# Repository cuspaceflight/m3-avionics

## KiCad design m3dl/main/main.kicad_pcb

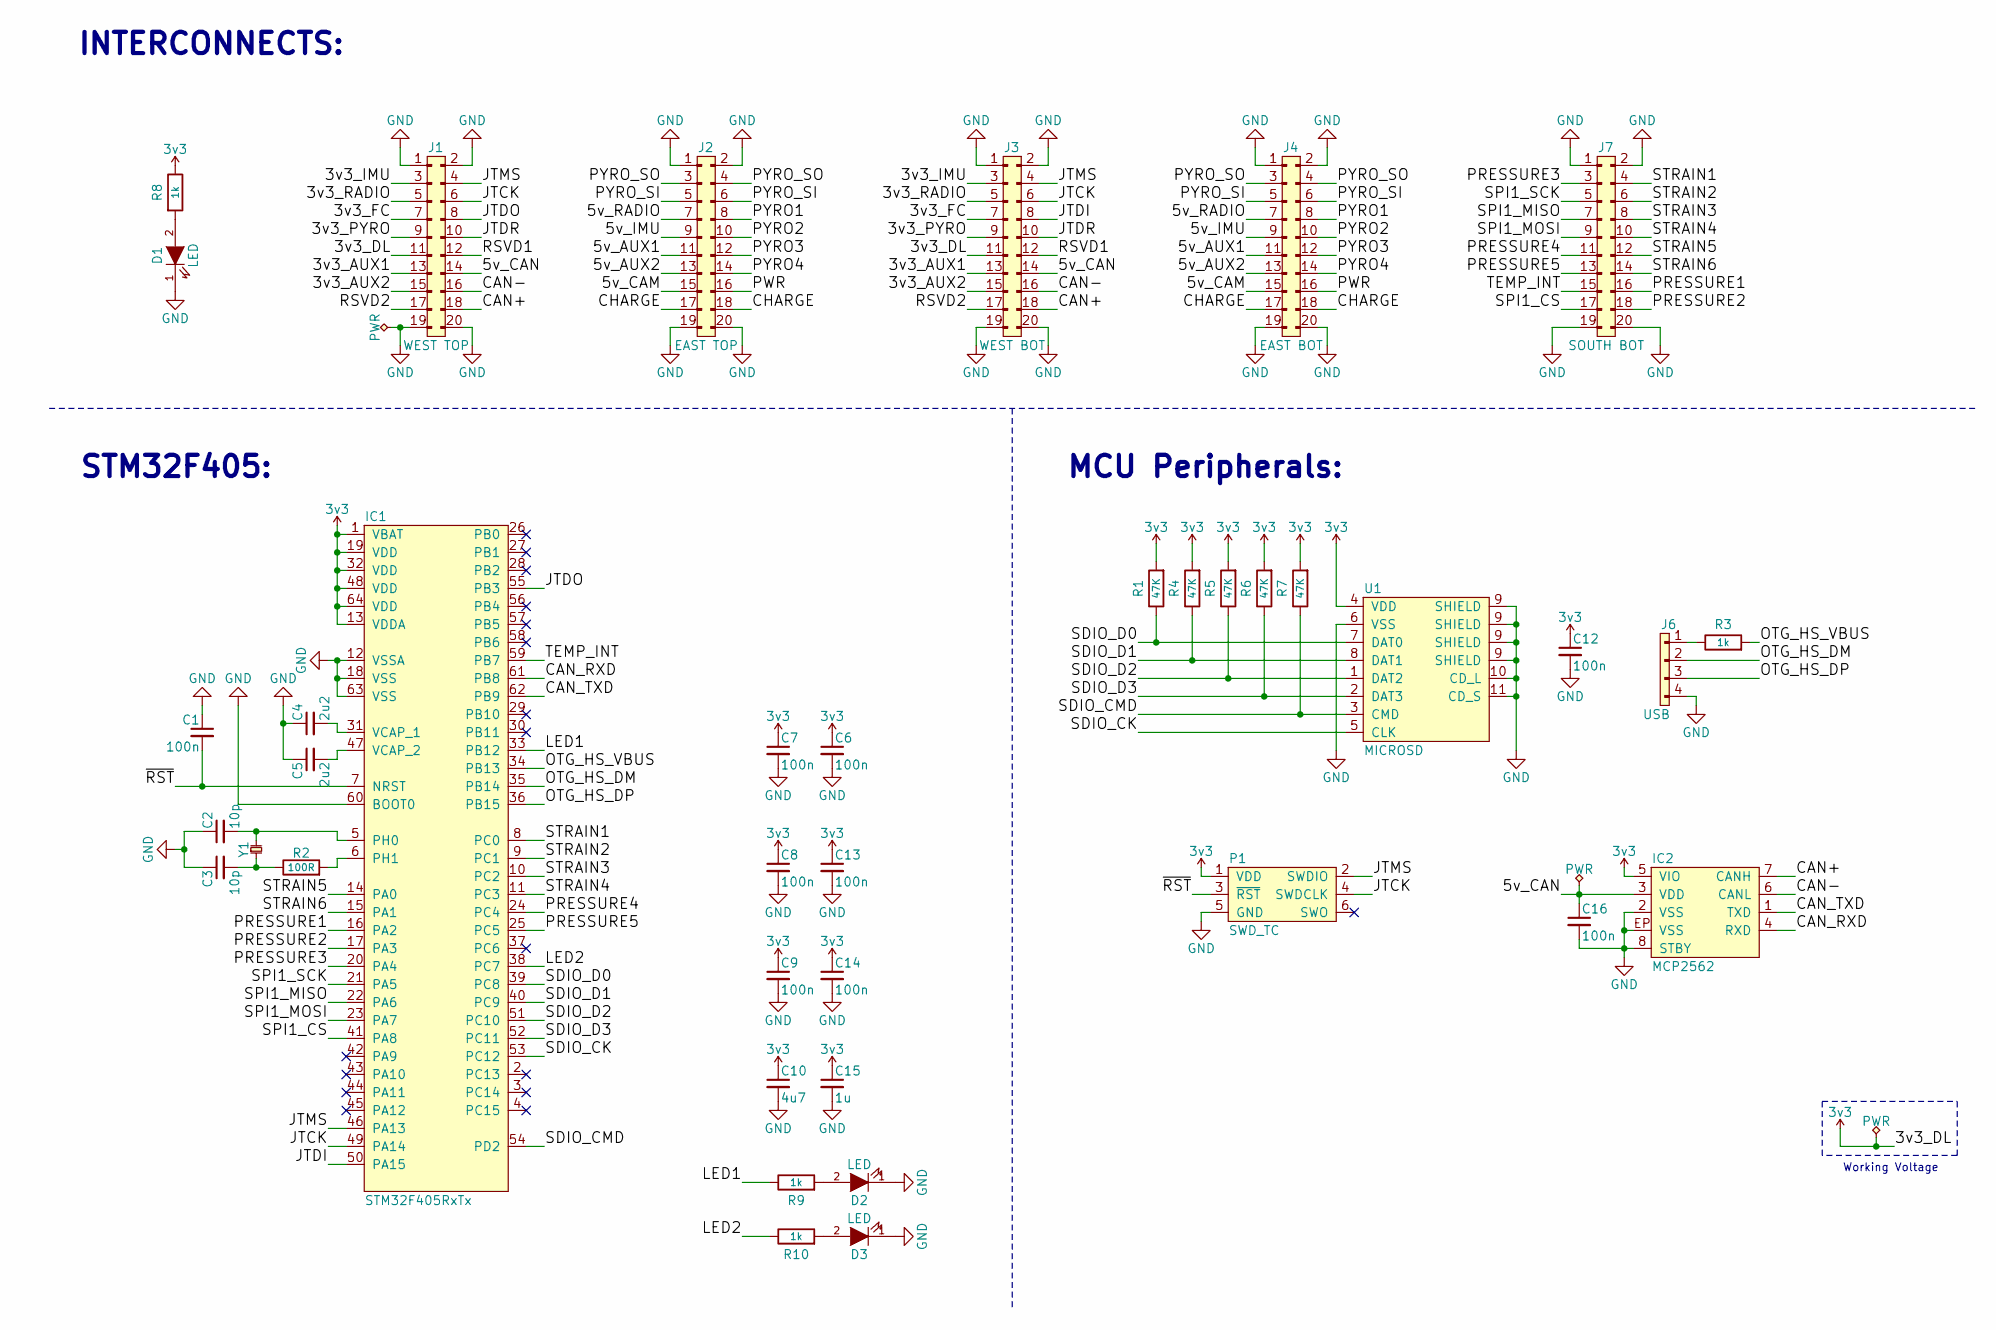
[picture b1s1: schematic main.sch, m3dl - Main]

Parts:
C1, C6, C7, C8, C9, C12, C13, C14, C16: 100n; C_0603; Farnell 2496834
C2, C3: 10p; C_0603; Farnell 2309035
C4, C5: 2u2; C_0603; Farnell 1797012
C10: 4u7; C_0603; Farnell 2496930
C15: 1u; C_0603; Farnell 1865556
D1, D2: LED; 0603-LED; Farnell 2290328
D3: LED; 0603-LED; Farnell 2290329
IC1: STM32F405RxTx; LQFP-64; Farnell 2064363
IC2: MCP2562; DFN-8-EP-MICROCHIP; Farnell 2448755
J1: WEST TOP; TFML-110-02-L-D
J2: EAST TOP; TFML-110-02-L-D
J3: WEST BOT; SFML-110-02-L-D-LC
J4: EAST BOT; SFML-110-02-L-D-LC
J6: USB; Connector_Molex_PicoBlade_53261-0471; Farnell 1125374
J7: SOUTH BOT; SFML-110-02-L-D-LC
P1: SWD_TC; TC2030-NL
R1, R4, R5, R6, R7: 47K; R_0603; Farnell 9238689
R2: 100R; R_0603; Farnell 2502395
R3, R8, R9, R10: 1k; 0603-L; Farnell 2309108
U1: MICROSD; MICROSD_MOLEX_503398-1892; Farnell 2358234
Y1: 26MHz; XTAL-20x16; Farnell 2506952

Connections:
3v3: C6.1, C7.1, C8.1, C9.1, C10.1, C12.1, C13.1, C14.1, C15.1, IC1.1 (VBAT), IC1.13 (VDDA), IC1.19 (VDD), IC1.32 (VDD), IC1.48 (VDD), IC1.64 (VDD), IC2.5 (VIO), J1.11, J3.11, P1.1 (VDD), R1.2, R4.2, R5.2, R6.2, R7.2, R8.1, U1.4 (VDD)
/3v3_AUX1: J1.13, J3.13
/3v3_AUX2: J1.15, J3.15
/3v3_FC: J1.7, J3.7
/3v3_IMU: J1.3, J3.3
/3v3_PYRO: J1.9, J3.9
/3v3_RADIO: J1.5, J3.5
/5v_AUX1: J2.11, J4.11
/5v_AUX2: J2.13, J4.13
/5v_CAM: J2.15, J4.15
/5v_CAN: C16.1, IC2.3 (VDD), J1.14, J3.14
/5v_IMU: J2.9, J4.9
/5v_RADIO: J2.7, J4.7
/CAN+: IC2.7 (CANH), J1.18, J3.18
/CAN-: IC2.6 (CANL), J1.16, J3.16
/CAN_RXD: IC1.61 (PB8), IC2.4 (RXD)
/CAN_TXD: IC1.62 (PB9), IC2.1 (TXD)
/CHARGE: J2.17, J2.18, J4.17, J4.18
/JTCK: IC1.49 (PA14), J1.6, J3.6, P1.4 (SWDCLK)
/JTDI: IC1.50 (PA15), J3.8
/JTDO: IC1.55 (PB3), J1.8
/JTDR: J1.10, J3.10
/JTMS: IC1.46 (PA13), J1.4, J3.4, P1.2 (SWDIO)
/LED1: IC1.33 (PB12), R9.1
/LED2: IC1.38 (PC7), R10.1
/OTG_HS_DM: IC1.35 (PB14), J6.2
/OTG_HS_DP: IC1.36 (PB15), J6.3
/OTG_HS_VBUS: IC1.34 (PB13), R3.2
/PRESSURE1: IC1.16 (PA2), J7.16
/PRESSURE2: IC1.17 (PA3), J7.18
/PRESSURE3: IC1.20 (PA4), J7.3
/PRESSURE4: IC1.24 (PC4), J7.11
/PRESSURE5: IC1.25 (PC5), J7.13
/PWR: J2.16, J4.16
/PYRO1: J2.8, J4.8
/PYRO2: J2.10, J4.10
/PYRO3: J2.12, J4.12
/PYRO4: J2.14, J4.14
/PYRO_SI: J2.5, J2.6, J4.5, J4.6
/PYRO_SO: J2.3, J2.4, J4.3, J4.4
/RSVD1: J1.12, J3.12
/RSVD2: J1.17, J3.17
/SDIO_CK: IC1.53 (PC12), U1.5 (CLK)
/SDIO_CMD: IC1.54 (PD2), R7.1, U1.3 (CMD)
/SDIO_D0: IC1.39 (PC8), R1.1, U1.7 (DAT0)
/SDIO_D1: IC1.40 (PC9), R4.1, U1.8 (DAT1)
/SDIO_D2: IC1.51 (PC10), R5.1, U1.1 (DAT2)
/SDIO_D3: IC1.52 (PC11), R6.1, U1.2 (DAT3)
/SPI1_CS: IC1.41 (PA8), J7.17
/SPI1_MISO: IC1.22 (PA6), J7.7
/SPI1_MOSI: IC1.23 (PA7), J7.9
/SPI1_SCK: IC1.21 (PA5), J7.5
/STRAIN1: IC1.8 (PC0), J7.4
/STRAIN2: IC1.9 (PC1), J7.6
/STRAIN3: IC1.10 (PC2), J7.8
/STRAIN4: IC1.11 (PC3), J7.10
/STRAIN5: IC1.14 (PA0), J7.12
/STRAIN6: IC1.15 (PA1), J7.14
/TEMP_INT: IC1.59 (PB7), J7.15
/~RST: C1.2, IC1.7 (NRST), P1.3 (~RST)
GND: C1.1, C2.1, C3.1, C4.1, C5.1, C6.2, C7.2, C8.2, C9.2, C10.2, C12.2, C13.2, C14.2, C15.2, C16.2, D1.1 (K), D2.1 (K), D3.1 (K), IC1.12 (VSSA), IC1.18 (VSS), IC1.60 (BOOT0), IC1.63 (VSS), IC2.2 (VSS), IC2.8 (STBY), IC2.EP (VSS), J1.1, J1.2, J1.19, J1.20, J2.1, J2.2, J2.19, J2.20, J3.1, J3.2, J3.19, J3.20, J4.1, J4.2, J4.19, J4.20, J6.4, J7.1, J7.2, J7.19, J7.20, P1.5 (GND), U1.6 (VSS), U1.9 (SHIELD), U1.10 (CD_L), U1.11 (CD_S)
unnamed: C2.2, IC1.5 (PH0), Y1.2
unnamed: C3.2, R2.1, Y1.1
unnamed: C4.2, IC1.31 (VCAP_1)
unnamed: C5.2, IC1.47 (VCAP_2)
unnamed: D1.2 (A), R8.2
unnamed: D2.2 (A), R9.2
unnamed: D3.2 (A), R10.2
unnamed: IC1.6 (PH1), R2.2
unnamed: J6.1, R3.1

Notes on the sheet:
STM32F405:
MCU Peripherals:
Working Voltage
INTERCONNECTS:

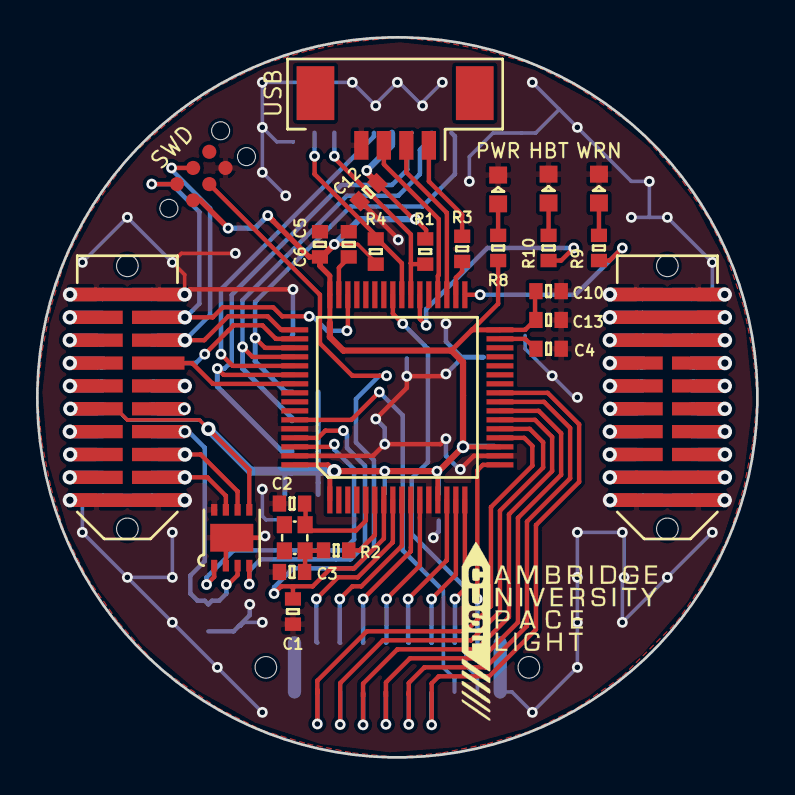
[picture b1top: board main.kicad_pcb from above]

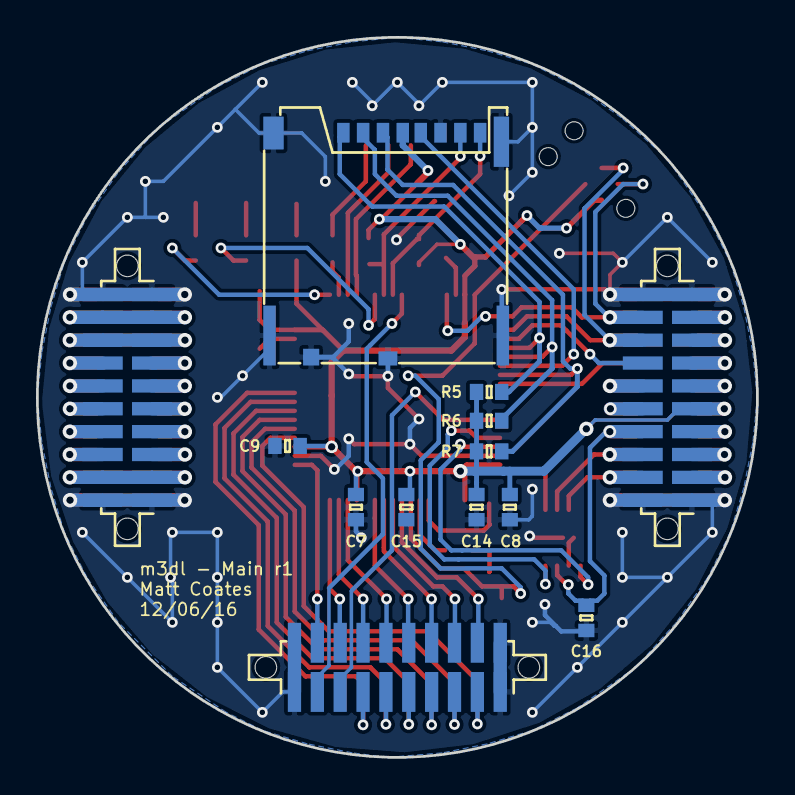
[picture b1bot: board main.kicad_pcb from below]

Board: 2 copper layers, 40.0 x 40.0 mm, 39 parts (13 on the bottom side), 70 nets.

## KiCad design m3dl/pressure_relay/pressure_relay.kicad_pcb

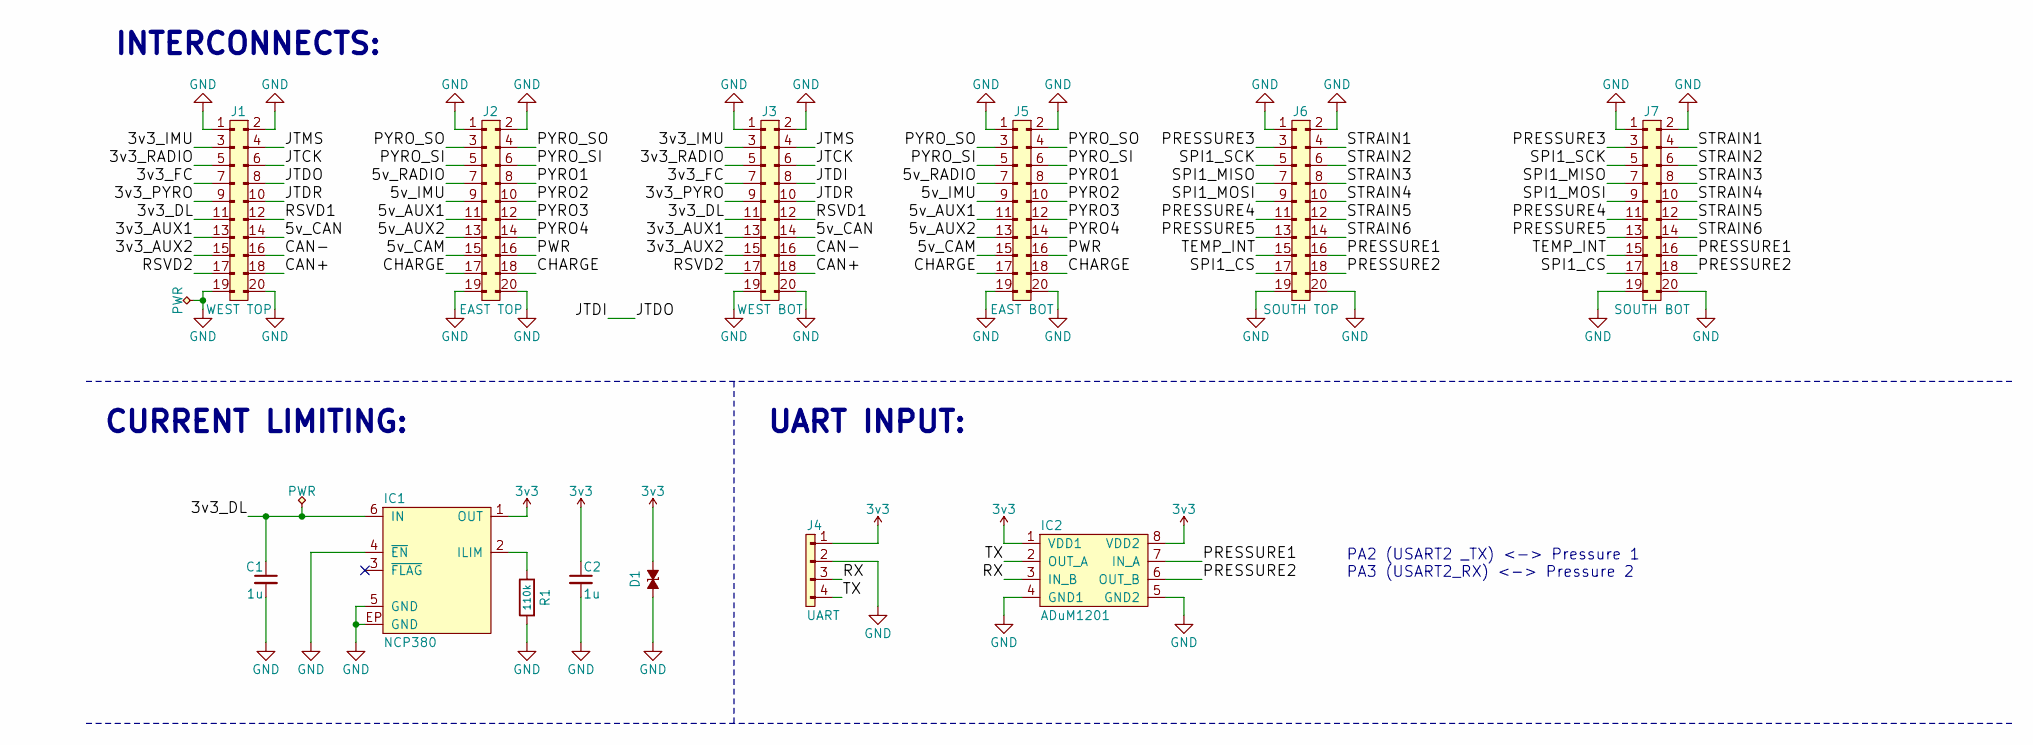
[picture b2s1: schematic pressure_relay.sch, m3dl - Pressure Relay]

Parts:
C1, C2: 1u; 0402-L; Farnell 2346884
D1: ESD_DIODE; 0402; Farnell 2368169
IC1: NCP380; DFN-6-EP-ONSEMI; Farnell 2464412
IC2: ADuM1201; SOIC-8; Farnell 1078202
J1: WEST TOP; TFML-110-02-L-D
J2: EAST TOP; TFML-110-02-L-D
J3: WEST BOT; SFML-110-02-L-D-LC
J4: UART; S04B-PASK-2; Farnell 1830749
J5: EAST BOT; SFML-110-02-L-D-LC
J6: SOUTH TOP; TFML-110-02-L-D
J7: SOUTH BOT; SFML-110-02-L-D-LC
R1: 110k; 0402-L; Farnell 2502502

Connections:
3v3: C2.1, D1.2, IC1.1 (OUT), IC2.1 (VDD1), IC2.8 (VDD2), J4.1
/3v3_AUX1: J1.13, J3.13
/3v3_AUX2: J1.15, J3.15
/3v3_DL: C1.1, IC1.6 (IN), J1.11, J3.11
/3v3_FC: J1.7, J3.7
/3v3_IMU: J1.3, J3.3
/3v3_PYRO: J1.9, J3.9
/3v3_RADIO: J1.5, J3.5
/5v_AUX1: J2.11, J5.11
/5v_AUX2: J2.13, J5.13
/5v_CAM: J2.15, J5.15
/5v_CAN: J1.14, J3.14
/5v_IMU: J2.9, J5.9
/5v_RADIO: J2.7, J5.7
/CAN+: J1.18, J3.18
/CAN-: J1.16, J3.16
/CHARGE: J2.17, J2.18, J5.17, J5.18
/JTCK: J1.6, J3.6
/JTDI: J1.8, J3.8
/JTDR: J1.10, J3.10
/JTMS: J1.4, J3.4
/PRESSURE1: IC2.7 (IN_A), J6.16, J7.16
/PRESSURE2: IC2.6 (OUT_B), J6.18, J7.18
/PRESSURE3: J6.3, J7.3
/PRESSURE4: J6.11, J7.11
/PRESSURE5: J6.13, J7.13
/PWR: J2.16, J5.16
/PYRO1: J2.8, J5.8
/PYRO2: J2.10, J5.10
/PYRO3: J2.12, J5.12
/PYRO4: J2.14, J5.14
/PYRO_SI: J2.5, J2.6, J5.5, J5.6
/PYRO_SO: J2.3, J2.4, J5.3, J5.4
/RSVD1: J1.12, J3.12
/RSVD2: J1.17, J3.17
/RX: IC2.3 (IN_B), J4.3
/SPI1_CS: J6.17, J7.17
/SPI1_MISO: J6.7, J7.7
/SPI1_MOSI: J6.9, J7.9
/SPI1_SCK: J6.5, J7.5
/STRAIN1: J6.4, J7.4
/STRAIN2: J6.6, J7.6
/STRAIN3: J6.8, J7.8
/STRAIN4: J6.10, J7.10
/STRAIN5: J6.12, J7.12
/STRAIN6: J6.14, J7.14
/TEMP_INT: J6.15, J7.15
/TX: IC2.2 (OUT_A), J4.4
GND: C1.2, C2.2, D1.1, IC1.4 (~EN), IC1.5 (GND), IC1.EP (GND), IC2.4 (GND1), IC2.5 (GND2), J1.1, J1.2, J1.19, J1.20, J2.1, J2.2, J2.19, J2.20, J3.1, J3.2, J3.19, J3.20, J4.2, J5.1, J5.2, J5.19, J5.20, J6.1, J6.2, J6.19, J6.20, J7.1, J7.2, J7.19, J7.20, R1.2
unnamed: IC1.2 (ILIM), R1.1

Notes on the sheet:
INTERCONNECTS:
CURRENT LIMITING:
UART INPUT:
PA2 (USART2 _TX) <-> Pressure 1 PA3 (USART2_RX) <-> Pressure 2

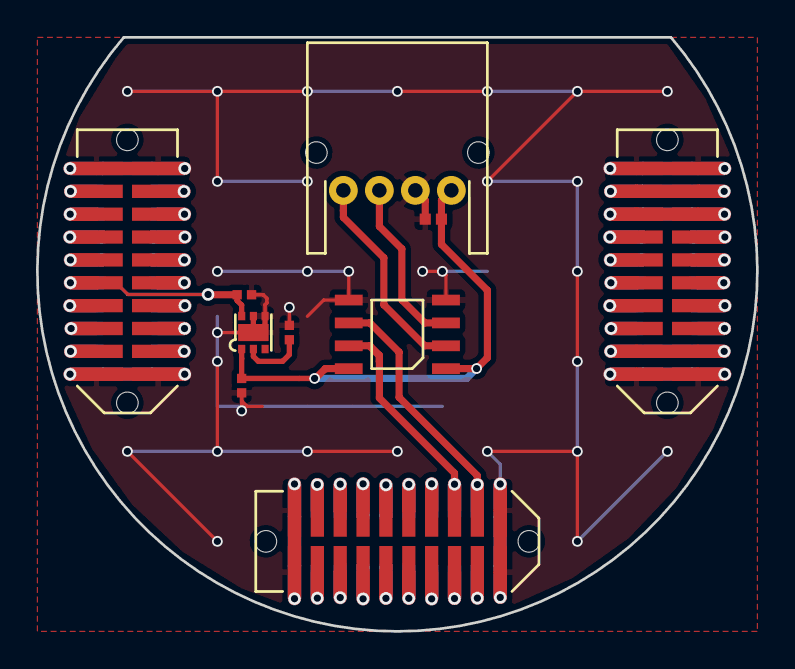
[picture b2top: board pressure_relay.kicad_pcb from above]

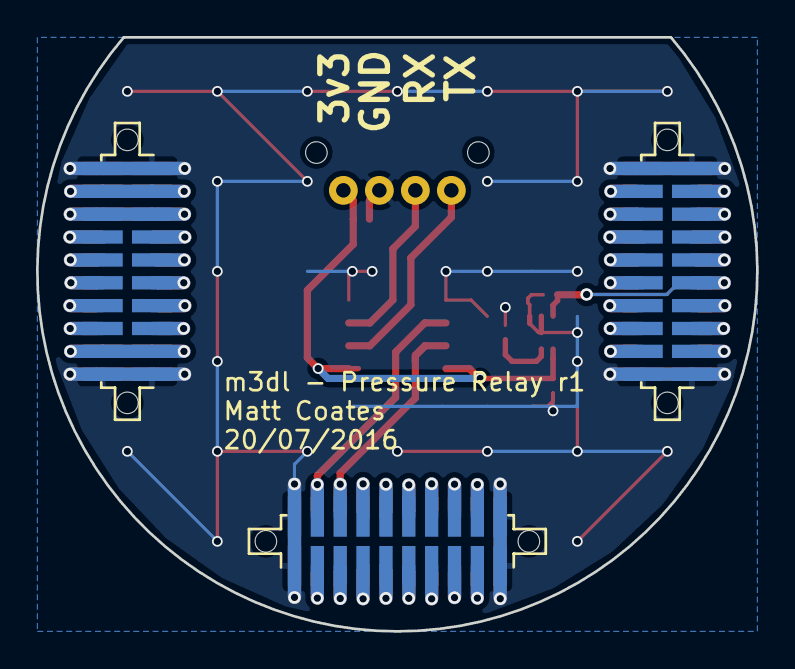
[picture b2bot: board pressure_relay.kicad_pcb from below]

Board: 2 copper layers, 40.0 x 33.0 mm, 13 parts (3 on the bottom side), 50 nets.

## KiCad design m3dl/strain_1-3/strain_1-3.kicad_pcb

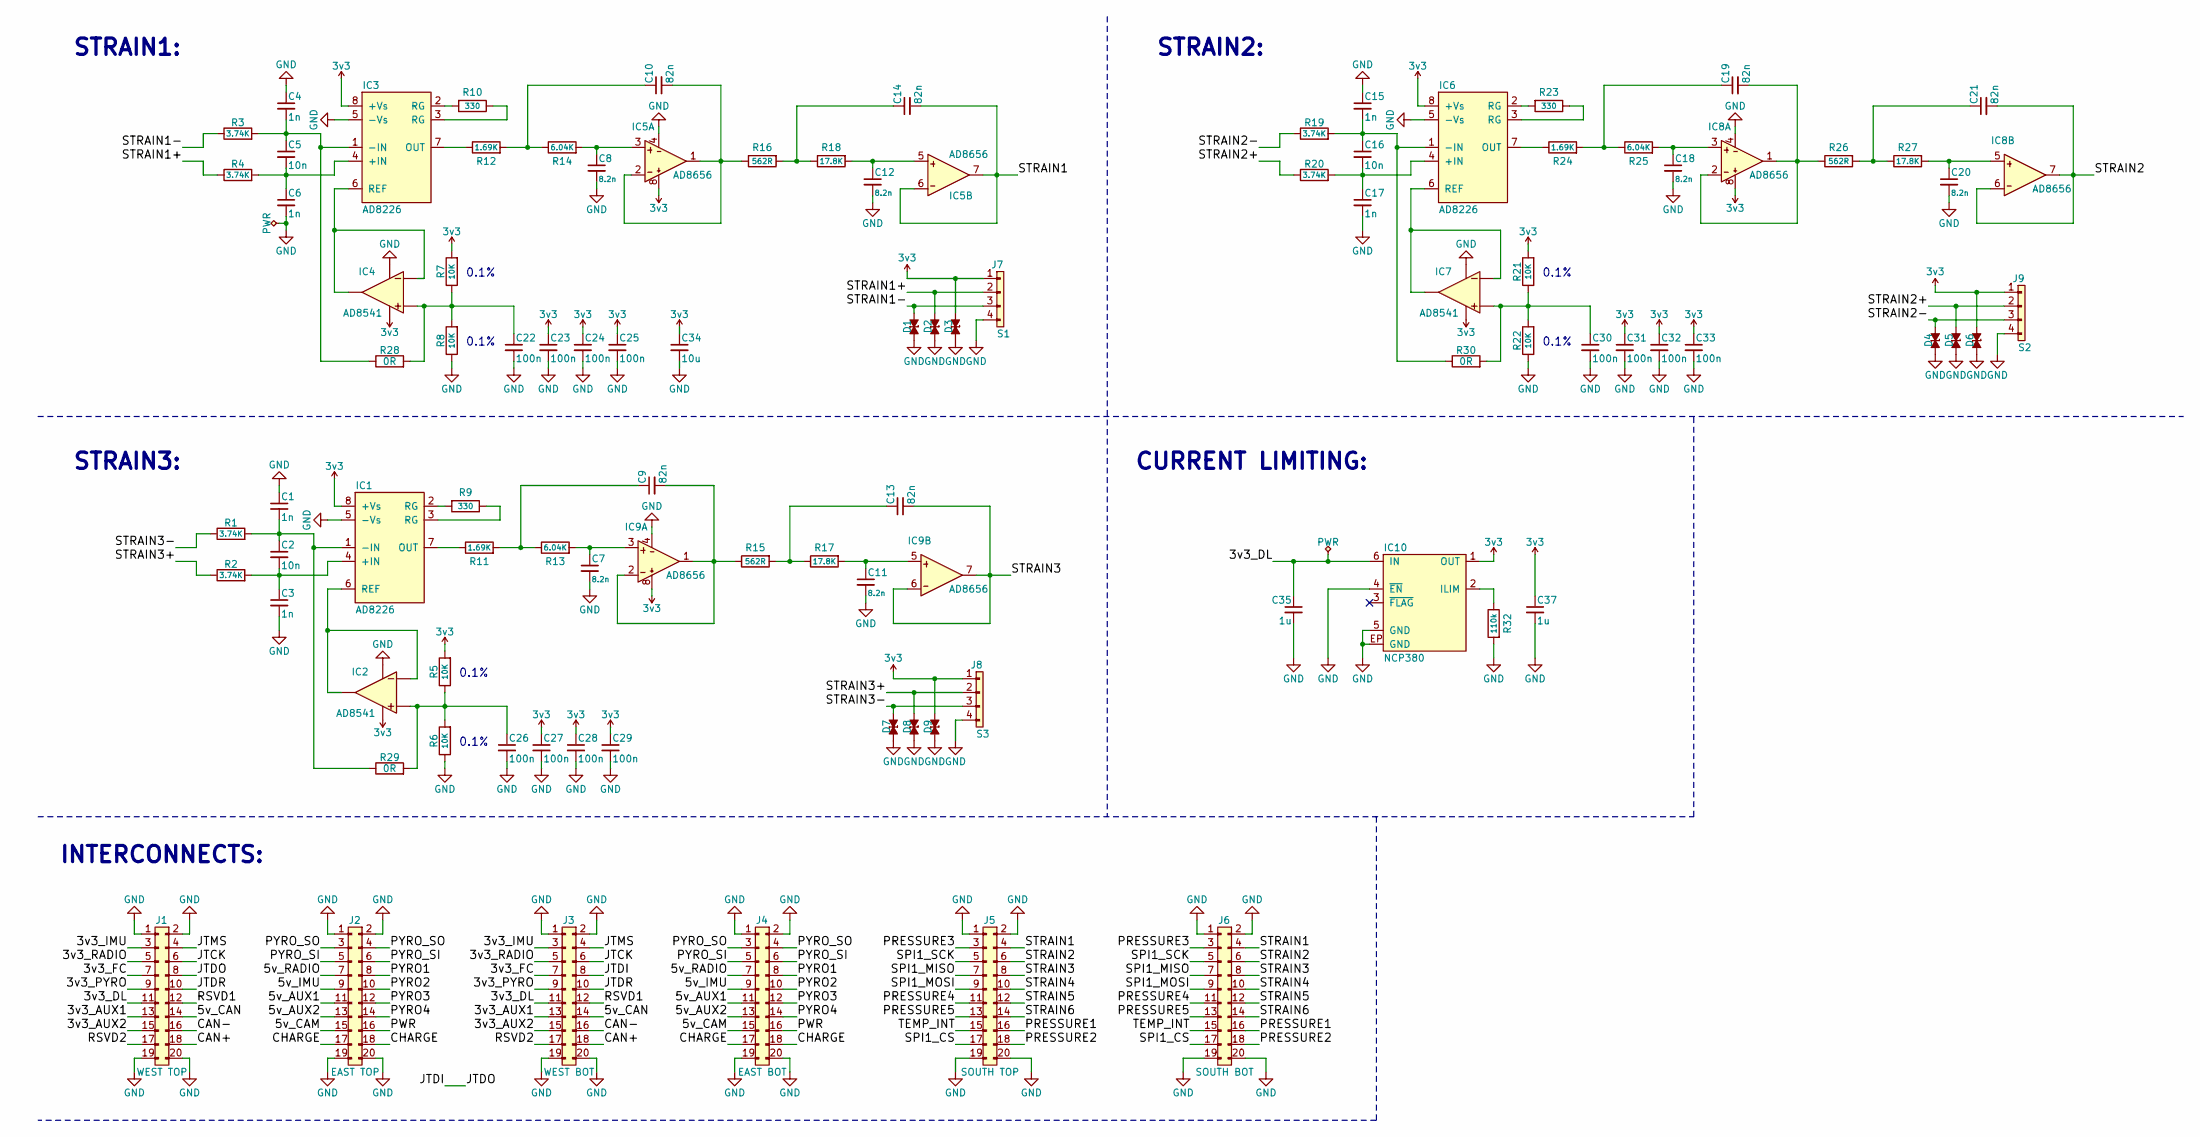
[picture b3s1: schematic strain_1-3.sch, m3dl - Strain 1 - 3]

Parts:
C1, C3, C4, C6, C15, C17: 1n; C_0603; Farnell 1813443
C2, C5, C16: 10n; C_0603; Farnell 1457729
C7, C8, C11, C12, C18, C20: 8.2n; C_0603; Farnell 1865464
C9, C10, C13, C14, C19, C21: 82n; C_0603; Farnell 1865539
C22, C23, C24, C25, C26, C27, C28, C29, C30, C31, C32, C33: 100n; 0603-L; Farnell 2496834
C34: 10u; 0603-L; Farnell 2211164
C35, C37: 1u; 0402-L; Farnell 2346884
D1, D2, D3, D4, D5, D6, D7, D8, D9: ESD_DIODE; 0402; Farnell 2368169
IC1, IC3, IC6: AD8226; MSOP-8; Farnell 2462026
IC2, IC4, IC7: AD8541; SC-70-5; Farnell 1333254
IC5, IC8, IC9: AD8656; MSOP-8; Farnell 1858055
IC10: NCP380; DFN-6-EP-ONSEMI; Farnell 2464412
J1: WEST TOP; TFML-110-02-L-D
J2: EAST TOP; TFML-110-02-L-D
J3: WEST BOT; SFML-110-02-L-D-LC
J4: EAST BOT; SFML-110-02-L-D-LC
J5: SOUTH TOP; TFML-110-02-L-D
J6: SOUTH BOT; SFML-110-02-L-D-LC
J7: S1; Connector_Molex_PicoBlade_53048-0410
J8: S3; Connector_Molex_PicoBlade_53048-0410
J9: S2; Connector_Molex_PicoBlade_53048-0410
R1, R2, R3, R4, R19, R20: 3.74K; R_0603; Farnell 2059366
R5, R6, R7, R8, R21, R22: 10K; R_0603; Farnell 1697388
R9, R10, R23: 330; R_0603; Farnell 2502447
R11, R12, R24: 1.69K; R_0603; Farnell 2059339
R13, R14, R25: 6.04K; R_0603; Farnell 2059386
R15, R16, R26: 562R; R_0603; Farnell 1170763
R17, R18, R27: 17.8K; R_0603; Farnell 1170912
R28, R29, R30: 0R; 0603; Farnell 9331662
R32: 110k; 0402-L; Farnell 2502502

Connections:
3v3: C23.1, C24.1, C25.1, C27.1, C28.1, C29.1, C31.1, C32.1, C33.1, C34.1, C37.1, D3.2, D6.2, D9.2, IC1.8 (+Vs), IC2.5 (V+), IC3.8 (+Vs), IC4.5 (V+), IC5.8 (V+), IC6.8 (+Vs), IC7.5 (V+), IC8.8 (V+), IC9.8 (V+), IC10.1 (OUT), J7.1, J8.1, J9.1, R5.2, R7.2, R21.2
/3v3_AUX1: J1.13, J3.13
/3v3_AUX2: J1.15, J3.15
/3v3_DL: C35.1, IC10.6 (IN), J1.11, J3.11
/3v3_FC: J1.7, J3.7
/3v3_IMU: J1.3, J3.3
/3v3_PYRO: J1.9, J3.9
/3v3_RADIO: J1.5, J3.5
/5v_AUX1: J2.11, J4.11
/5v_AUX2: J2.13, J4.13
/5v_CAM: J2.15, J4.15
/5v_CAN: J1.14, J3.14
/5v_IMU: J2.9, J4.9
/5v_RADIO: J2.7, J4.7
/CAN+: J1.18, J3.18
/CAN-: J1.16, J3.16
/CHARGE: J2.17, J2.18, J4.17, J4.18
/JTCK: J1.6, J3.6
/JTDI: J1.8, J3.8
/JTDR: J1.10, J3.10
/JTMS: J1.4, J3.4
/PRESSURE1: J5.16, J6.16
/PRESSURE2: J5.18, J6.18
/PRESSURE3: J5.3, J6.3
/PRESSURE4: J5.11, J6.11
/PRESSURE5: J5.13, J6.13
/PWR: J2.16, J4.16
/PYRO1: J2.8, J4.8
/PYRO2: J2.10, J4.10
/PYRO3: J2.12, J4.12
/PYRO4: J2.14, J4.14
/PYRO_SI: J2.5, J2.6, J4.5, J4.6
/PYRO_SO: J2.3, J2.4, J4.3, J4.4
/RSVD1: J1.12, J3.12
/RSVD2: J1.17, J3.17
/SPI1_CS: J5.17, J6.17
/SPI1_MISO: J5.7, J6.7
/SPI1_MOSI: J5.9, J6.9
/SPI1_SCK: J5.5, J6.5
/STRAIN1: C14.2, IC5.6 (-IN), IC5.7 (OUT), J5.4, J6.4
/STRAIN1+: D2.2, J7.2, R4.1
/STRAIN1-: D1.2, J7.3, R3.1
/STRAIN2: C21.2, IC8.6 (-IN), IC8.7 (OUT), J5.6, J6.6
/STRAIN2+: D5.2, J9.2, R20.1
/STRAIN2-: D4.2, J9.3, R19.1
/STRAIN3: C13.2, IC9.6 (-IN), IC9.7 (OUT), J5.8, J6.8
/STRAIN3+: D8.2, J8.2, R2.1
/STRAIN3-: D7.2, J8.3, R1.1
/STRAIN4: J5.10, J6.10
/STRAIN5: J5.12, J6.12
/STRAIN6: J5.14, J6.14
/TEMP_INT: J5.15, J6.15
GND: C1.1, C3.2, C4.1, C6.2, C7.2, C8.2, C11.2, C12.2, C15.1, C17.2, C18.2, C20.2, C22.2, C23.2, C24.2, C25.2, C26.2, C27.2, C28.2, C29.2, C30.2, C31.2, C32.2, C33.2, C34.2, C35.2, C37.2, D1.1, D2.1, D3.1, D4.1, D5.1, D6.1, D7.1, D8.1, D9.1, IC1.5 (-Vs), IC2.2 (V-), IC3.5 (-Vs), IC4.2 (V-), IC5.4 (V-), IC6.5 (-Vs), IC7.2 (V-), IC8.4 (V-), IC9.4 (V-), IC10.4 (~EN), IC10.5 (GND), IC10.EP (GND), J1.1, J1.2, J1.19, J1.20, J2.1, J2.2, J2.19, J2.20, J3.1, J3.2, J3.19, J3.20, J4.1, J4.2, J4.19, J4.20, J5.1, J5.2, J5.19, J5.20, J6.1, J6.2, J6.19, J6.20, J7.4, J8.4, J9.4, R6.1, R8.1, R22.1, R32.2
unnamed: C1.2, C2.1, IC1.1 (-IN), R1.2, R29.1
unnamed: C2.2, C3.1, IC1.4 (+IN), R2.2
unnamed: C4.2, C5.1, IC3.1 (-IN), R3.2, R28.1
unnamed: C5.2, C6.1, IC3.4 (+IN), R4.2
unnamed: C7.1, IC9.3 (+IN), R13.2
unnamed: C8.1, IC5.3 (+IN), R14.2
unnamed: C9.1, R11.2, R13.1
unnamed: C9.2, IC9.1 (OUT), IC9.2 (-IN), R15.1
unnamed: C10.1, R12.2, R14.1
unnamed: C10.2, IC5.1 (OUT), IC5.2 (-IN), R16.1
unnamed: C11.1, IC9.5 (+IN), R17.2
unnamed: C12.1, IC5.5 (+IN), R18.2
unnamed: C13.1, R15.2, R17.1
unnamed: C14.1, R16.2, R18.1
unnamed: C15.2, C16.1, IC6.1 (-IN), R19.2, R30.1
unnamed: C16.2, C17.1, IC6.4 (+IN), R20.2
unnamed: C18.1, IC8.3 (+IN), R25.2
unnamed: C19.1, R24.2, R25.1
unnamed: C19.2, IC8.1 (OUT), IC8.2 (-IN), R26.1
unnamed: C20.1, IC8.5 (+IN), R27.2
unnamed: C21.1, R26.2, R27.1
unnamed: C22.1, IC4.3 (+), R7.1, R8.2, R28.2
unnamed: C26.1, IC2.3 (+), R5.1, R6.2, R29.2
unnamed: C30.1, IC7.3 (+), R21.1, R22.2, R30.2
unnamed: IC1.2 (RG), R9.2
unnamed: IC1.3 (RG), R9.1
unnamed: IC1.6 (REF), IC2.1 (OUT), IC2.4 (-)
unnamed: IC1.7 (OUT), R11.1
unnamed: IC3.2 (RG), R10.2
unnamed: IC3.3 (RG), R10.1
unnamed: IC3.6 (REF), IC4.1 (OUT), IC4.4 (-)
unnamed: IC3.7 (OUT), R12.1
unnamed: IC6.2 (RG), R23.2
unnamed: IC6.3 (RG), R23.1
unnamed: IC6.6 (REF), IC7.1 (OUT), IC7.4 (-)
unnamed: IC6.7 (OUT), R24.1
unnamed: IC10.2 (ILIM), R32.1

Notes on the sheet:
INTERCONNECTS:
STRAIN1:
STRAIN2:
STRAIN3:
0.1%
CURRENT LIMITING:

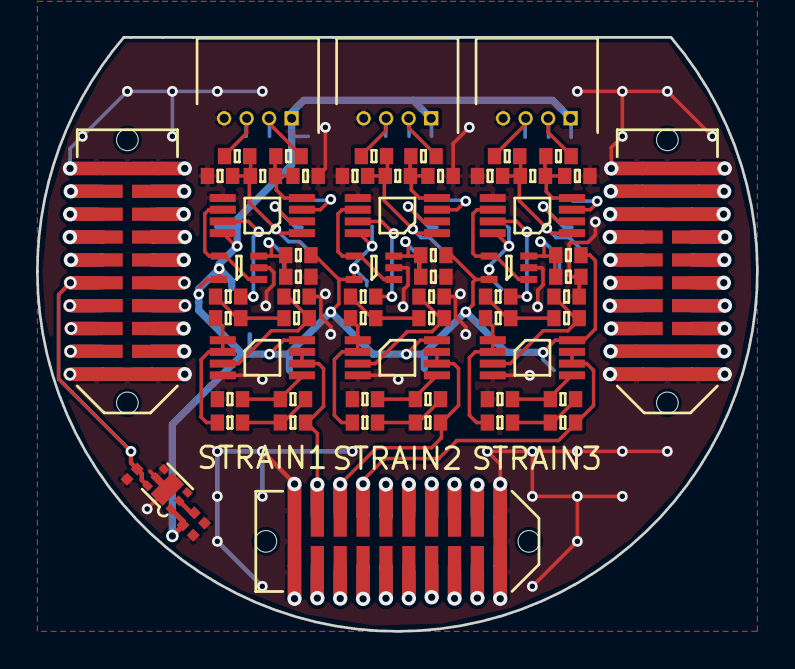
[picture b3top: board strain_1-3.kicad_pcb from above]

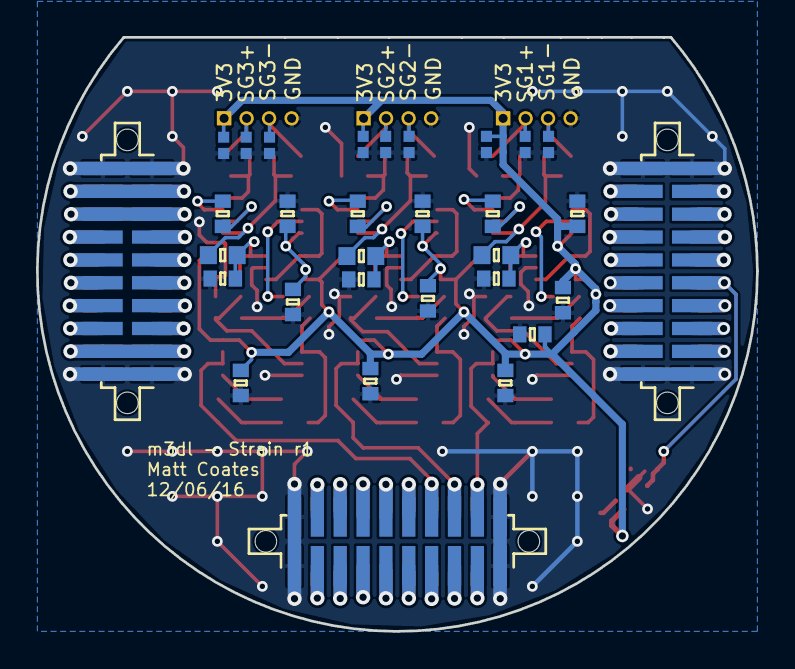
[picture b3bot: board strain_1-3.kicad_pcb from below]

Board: 2 copper layers, 40.0 x 33.0 mm, 95 parts (31 on the bottom side), 90 nets.
